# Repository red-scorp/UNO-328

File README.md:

# UNO/328 project

UNO/328 is a clone board of popular Arduino Uno board.
Main goal of the project is to improve EMC property of original board keeping it still simple and cheap to produce.

## Uno_v1.0

**Uno_v1.0** is version 1.0 of the board featuring CH340G USB to UART chip and ATMEGA328P as MCU.

Preview:

[Schematics in PDF format](doc/Uno_v1.0.pdf)

Features:

- Uno compatible board pinout
- Uno compatible MCU ATMEGA328P
- 2 layer board design
- alternative footprints for MCU: TQFP and HVQFN
- CH340G chip as USB to UART bridge
- modern microUSB connector
- possibly better EMC parameters (not yet tested)

CAM files are available.
BoM and PnP files for JLCPCB are available.

## Links

- CH340G Driver for Windows: [CH341SER_ZIP](http://www.wch.cn/download/CH341SER_ZIP.html)

## How to help

Your contributions as code, resources, or finances are welcome! Please contact me directly via email at andriy.golovnya@gmail.com or through my [GitHub profile](https://github.com/red-scorp).

If you'd like to make a financial contribution, you can donate via [PayPal](http://paypal.me/redscorp) or [Ko-Fi](http://ko-fi.com/redscorp). Your support is greatly appreciated.

Thanks in advance!

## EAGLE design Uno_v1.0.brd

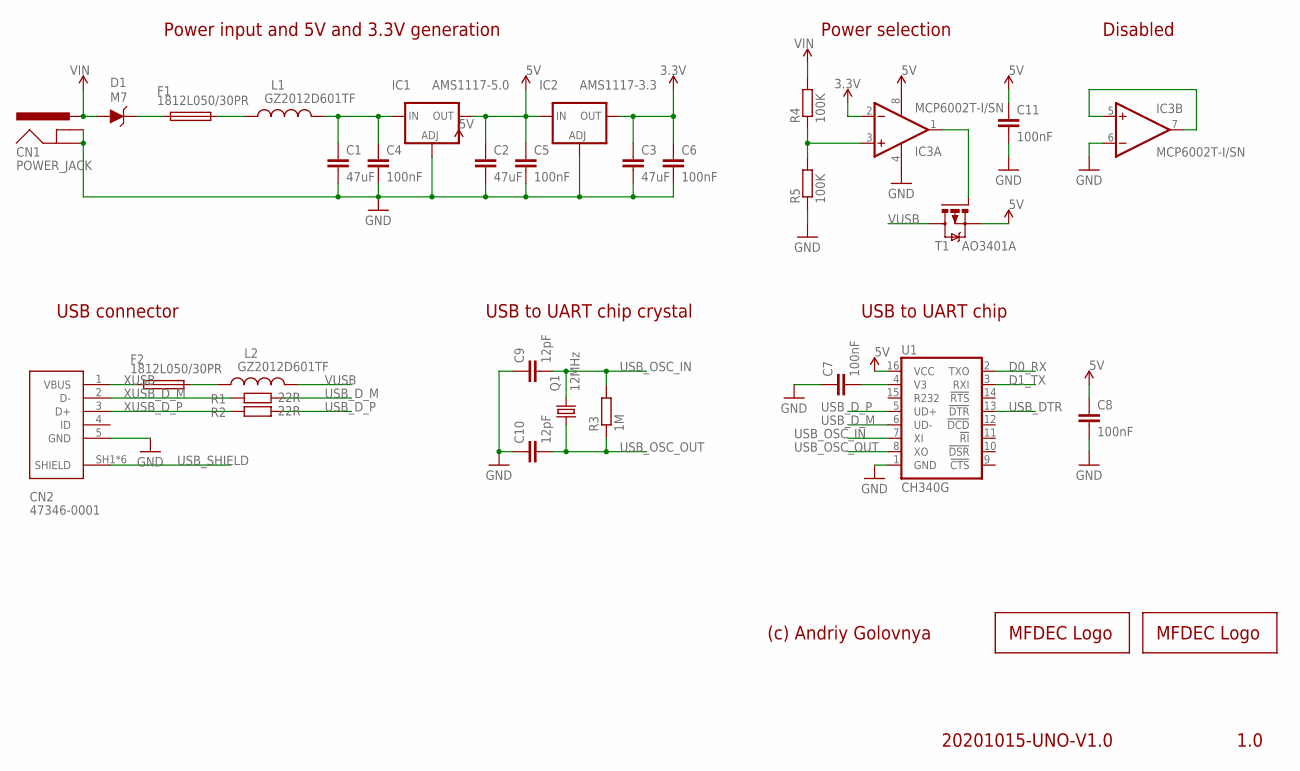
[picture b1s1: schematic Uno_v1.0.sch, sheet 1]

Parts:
C1, C2, C3: 47uF; C1206
C4, C5, C6, C7, C8, C11: 100nF; C0402
C9, C10: 12pF; C0402
CN1: POWER_JACK; POWER_JACK_PTH
CN2: 47346-0001; MOLEX_47346-0001
D1: M7; WE-TVSP_DO-214AC_UNIDIRECTIONAL
F1, F2: 1812L050/30PR; MF-SMDF050
IC1: AMS1117-5.0; SOT223
IC2: AMS1117-3.3; SOT223
IC3: MCP6002T-I/SN; SO08
L1, L2: GZ2012D601TF; WE-CBA_0805(W=4)
LOGO1: MFDECLOGO_SQ_10MM; MFDEC_SQ_10MM
LOGO2: MFDECLOGO_L_40MM; MFDEC_L_40MM
Q1: 12MHz; 3.2X2.5_KX-7
R1, R2: 22R; R0402
R3: 1M; R0402
R4, R5: 100K; R0402
T1: AO3401A; SOT23
U1: CH340G; SO016

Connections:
3.3V: C3.1, C6.1, IC2.4 (OUT), IC3.2 (-IN); also elsewhere on the board
5V: C2.1, C5.1, C8.1, C11.1, IC1.4 (OUT), IC2.3 (IN), IC3.8 (V+), T1.2 (S), U1.16 (VCC); also elsewhere on the board
D0_RX: U1.2 (TXO); also elsewhere on the board
D1_TX: U1.3 (RXI); also elsewhere on the board
unnamed: D1.1 (C), F1.1
unnamed: F1.2, L1.1
unnamed: F2.2, L2.1
unnamed: C7.2, U1.4 (V3)
unnamed: IC3.1 (OUT), T1.1 (G)
unnamed: IC3.3 (+IN), R4.1, R5.2
unnamed: C1.1, C4.1, IC1.3 (IN), L1.2
USB_DTR: U1.13 (!DTR); also elsewhere on the board
USB_D_M: R1.2, U1.6 (UD-)
USB_D_P: R2.2, U1.5 (UD+)
USB_OSC_IN: C9.2, Q1.3 (2), R3.2, U1.7 (XI)
USB_OSC_OUT: C10.2, Q1.1, R3.1, U1.8 (XO)
USB_SHIELD: CN2.SH1 (SHIELD), CN2.SH2 (SHIELD), CN2.SH3 (SHIELD), CN2.SH4 (SHIELD), CN2.SH5 (SHIELD), CN2.SH6 (SHIELD)
VIN: CN1.PWR, D1.2 (A), R4.2; also elsewhere on the board
VUSB: L2.2, T1.3 (D)
XUSB: CN2.1 (VBUS), F2.1
XUSB_D_M: CN2.2 (D-), R1.1
XUSB_D_P: CN2.3 (D+), R2.1

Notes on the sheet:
1.0
(c) Andriy Golovnya
20201015-UNO-V1.0
Power input and 5V and 3.3V generation
USB connector
USB to UART chip
USB to UART chip crystal
Power selection
Disabled

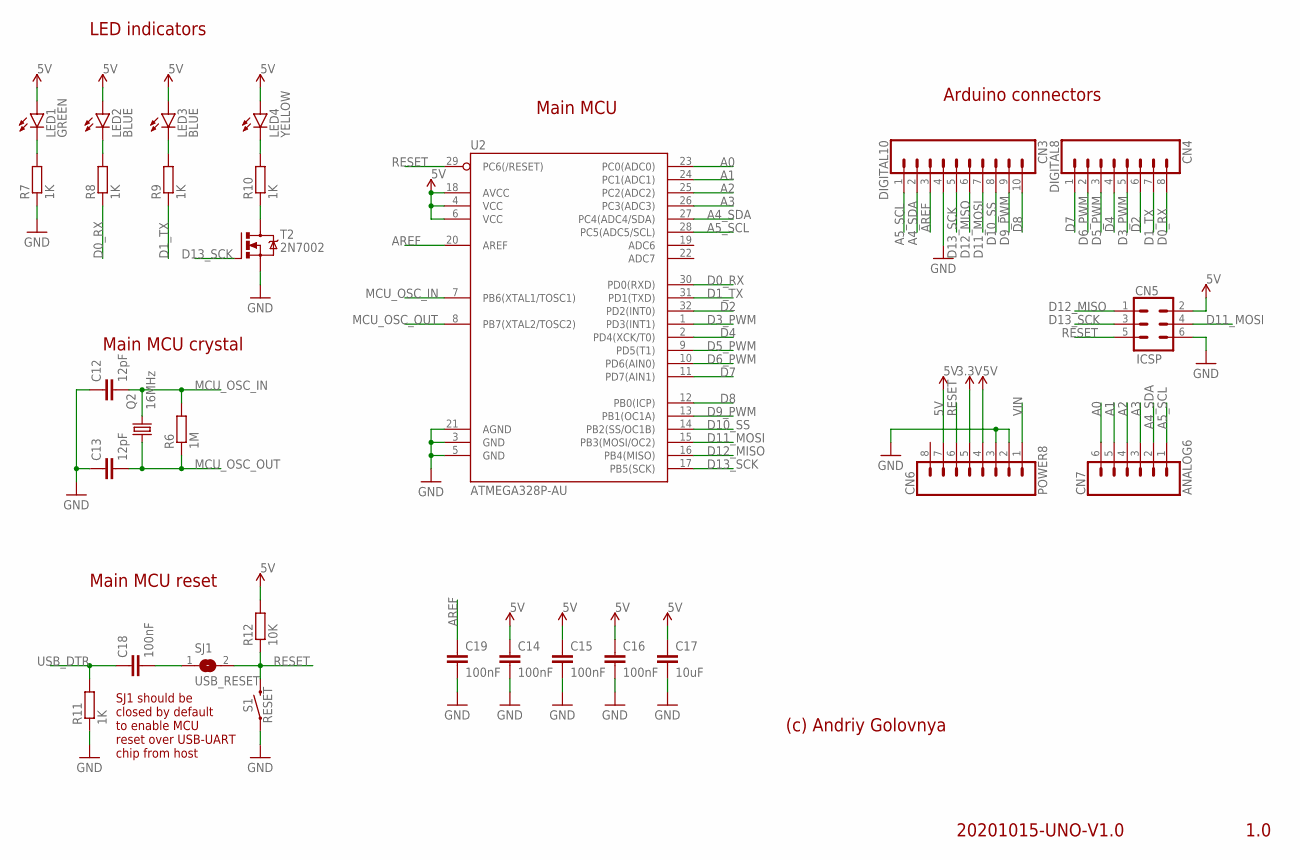
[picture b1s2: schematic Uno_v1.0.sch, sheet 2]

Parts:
C12, C13: 12pF; C0402
C14, C15, C16, C18, C19: 100nF; C0402
C17: 10uF; C0805
CN3: DIGITAL10; 1X10_NO_SILK
CN4: DIGITAL8; 1X08_NO_SILK
CN5: ICSP; 2X3-NS
CN6: POWER8; 1X08_NO_SILK
CN7: ANALOG6; 1X06_NO_SILK
LED1: GREEN; SML0603
LED2, LED3: BLUE; SML0603
LED4: YELLOW; SML0603
Q2: 16MHz; 3.2X2.5_KX-7
R6: 1M; R0402
R7, R8, R9, R10, R11: 1K; R0402
R12: 10K; R0402
S1: RESET; TACTILE_SWITCH_SMD_5.2MM
SJ1: USB_RESET; SJ
T2: 2N7002; SOT23
U2: ATMEGA328P-AU; TQFP32-08

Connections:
3.3V: CN6.5; also elsewhere on the board
5V: C14.1, C15.1, C16.1, C17.1, CN5.2, CN6.4, CN6.7, LED1.A, LED2.A, LED3.A, LED4.A, R12.2, U2.4 (VCC), U2.6 (VCC), U2.18 (AVCC); also elsewhere on the board
A0: CN7.6, U2.23 (PC0(ADC0)); also elsewhere on the board
A1: CN7.5, U2.24 (PC1(ADC1)); also elsewhere on the board
A2: CN7.4, U2.25 (PC2(ADC2)); also elsewhere on the board
A3: CN7.3, U2.26 (PC3(ADC3)); also elsewhere on the board
A4_SDA: CN3.2, CN7.2, U2.27 (PC4(ADC4/SDA)); also elsewhere on the board
A5_SCL: CN3.1, CN7.1, U2.28 (PC5(ADC5/SCL)); also elsewhere on the board
AREF: C19.1, CN3.3, U2.20 (AREF); also elsewhere on the board
D0_RX: CN4.8, R8.1, U2.30 (PD0(RXD)); also elsewhere on the board
D1_TX: CN4.7, R9.1, U2.31 (PD1(TXD)); also elsewhere on the board
D2: CN4.6, U2.32 (PD2(INT0)); also elsewhere on the board
D3_PWM: CN4.5, U2.1 (PD3(INT1)); also elsewhere on the board
D4: CN4.4, U2.2 (PD4(XCK/T0)); also elsewhere on the board
D5_PWM: CN4.3, U2.9 (PD5(T1)); also elsewhere on the board
D6_PWM: CN4.2, U2.10 (PD6(AIN0)); also elsewhere on the board
D7: CN4.1, U2.11 (PD7(AIN1)); also elsewhere on the board
D8: CN3.10, U2.12 (PB0(ICP)); also elsewhere on the board
D9_PWM: CN3.9, U2.13 (PB1(OC1A)); also elsewhere on the board
D10_SS: CN3.8, U2.14 (PB2(SS/OC1B)); also elsewhere on the board
D11_MOSI: CN3.7, CN5.4, U2.15 (PB3(MOSI/OC2)); also elsewhere on the board
D12_MISO: CN3.6, CN5.1, U2.16 (PB4(MISO)); also elsewhere on the board
D13_SCK: CN3.5, CN5.3, T2.1 (G), U2.17 (PB5(SCK)); also elsewhere on the board
MCU_OSC_IN: C12.2, Q2.3 (2), R6.2, U2.7 (PB6(XTAL1/TOSC1)); also elsewhere on the board
MCU_OSC_OUT: C13.2, Q2.1, R6.1, U2.8 (PB7(XTAL2/TOSC2)); also elsewhere on the board
unnamed: C18.2, SJ1.1
unnamed: LED1.C, R7.2
unnamed: LED3.C, R9.2
unnamed: LED2.C, R8.2
unnamed: LED4.C, R10.2
unnamed: R10.1, T2.3 (D)
RESET: CN5.5, CN6.6, R12.1, S1.3 (2), SJ1.2, U2.29 (PC6(/RESET)); also elsewhere on the board
USB_DTR: C18.1, R11.2; also elsewhere on the board
VIN: CN6.1; also elsewhere on the board

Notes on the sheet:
1.0
(c) Andriy Golovnya
20201015-UNO-V1.0
LED indicators
Main MCU
Main MCU reset
Arduino connectors
Main MCU crystal
SJ1 should be closed by default to enable MCU reset over USB-UART chip from host

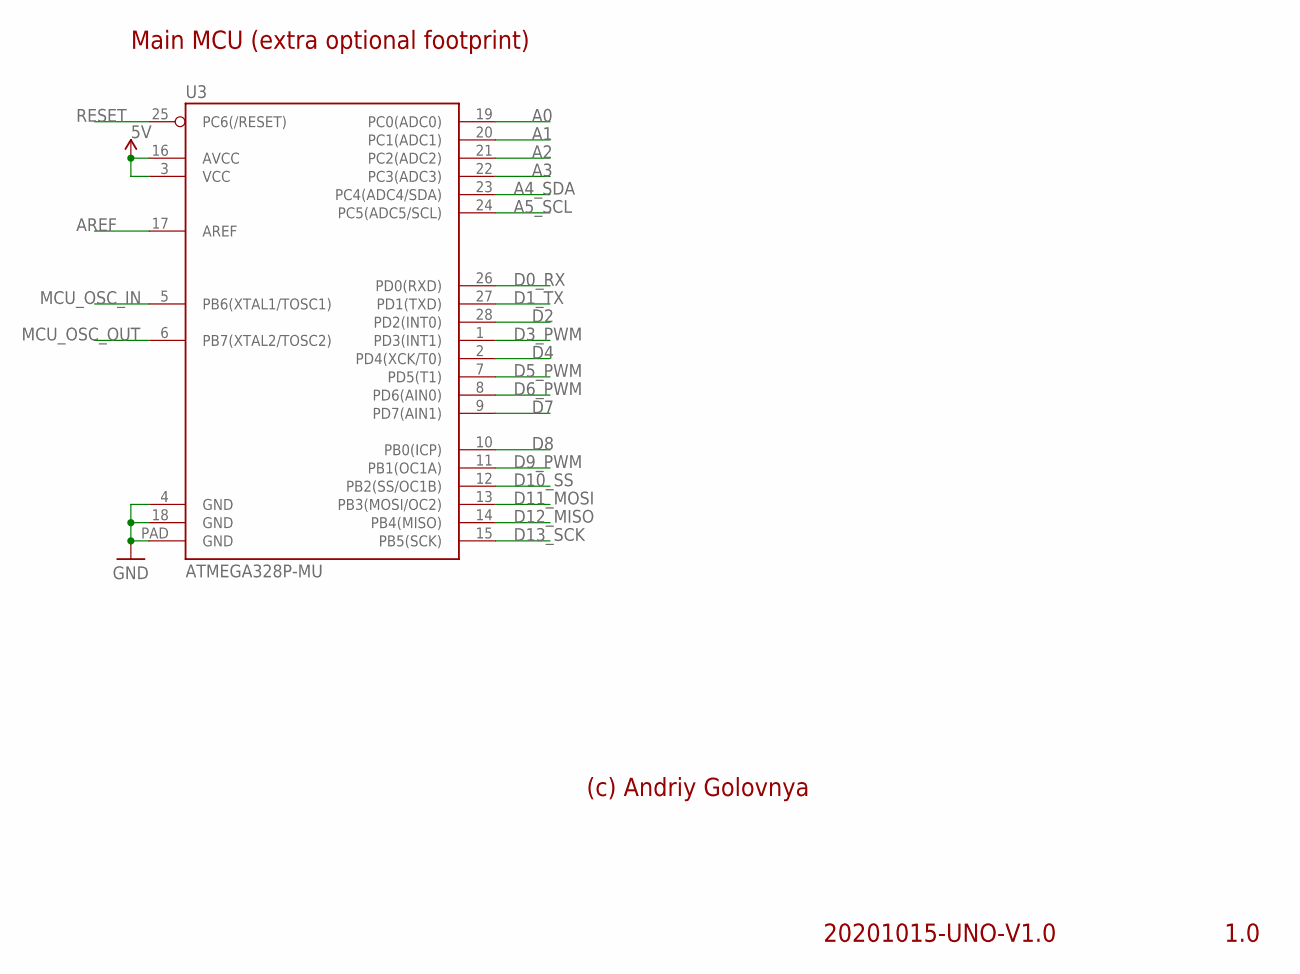
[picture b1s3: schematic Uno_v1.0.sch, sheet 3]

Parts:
U3: ATMEGA328P-MU; VQFN-28

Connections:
5V: U3.3 (VCC), U3.16 (AVCC); also elsewhere on the board
A0: U3.19 (PC0(ADC0)); also elsewhere on the board
A1: U3.20 (PC1(ADC1)); also elsewhere on the board
A2: U3.21 (PC2(ADC2)); also elsewhere on the board
A3: U3.22 (PC3(ADC3)); also elsewhere on the board
A4_SDA: U3.23 (PC4(ADC4/SDA)); also elsewhere on the board
A5_SCL: U3.24 (PC5(ADC5/SCL)); also elsewhere on the board
AREF: U3.17 (AREF); also elsewhere on the board
D0_RX: U3.26 (PD0(RXD)); also elsewhere on the board
D1_TX: U3.27 (PD1(TXD)); also elsewhere on the board
D2: U3.28 (PD2(INT0)); also elsewhere on the board
D3_PWM: U3.1 (PD3(INT1)); also elsewhere on the board
D4: U3.2 (PD4(XCK/T0)); also elsewhere on the board
D5_PWM: U3.7 (PD5(T1)); also elsewhere on the board
D6_PWM: U3.8 (PD6(AIN0)); also elsewhere on the board
D7: U3.9 (PD7(AIN1)); also elsewhere on the board
D8: U3.10 (PB0(ICP)); also elsewhere on the board
D9_PWM: U3.11 (PB1(OC1A)); also elsewhere on the board
D10_SS: U3.12 (PB2(SS/OC1B)); also elsewhere on the board
D11_MOSI: U3.13 (PB3(MOSI/OC2)); also elsewhere on the board
D12_MISO: U3.14 (PB4(MISO)); also elsewhere on the board
D13_SCK: U3.15 (PB5(SCK)); also elsewhere on the board
MCU_OSC_IN: U3.5 (PB6(XTAL1/TOSC1)); also elsewhere on the board
MCU_OSC_OUT: U3.6 (PB7(XTAL2/TOSC2)); also elsewhere on the board
RESET: U3.25 (PC6(/RESET)); also elsewhere on the board

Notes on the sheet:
1.0
(c) Andriy Golovnya
20201015-UNO-V1.0
Main MCU (extra optional footprint)

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
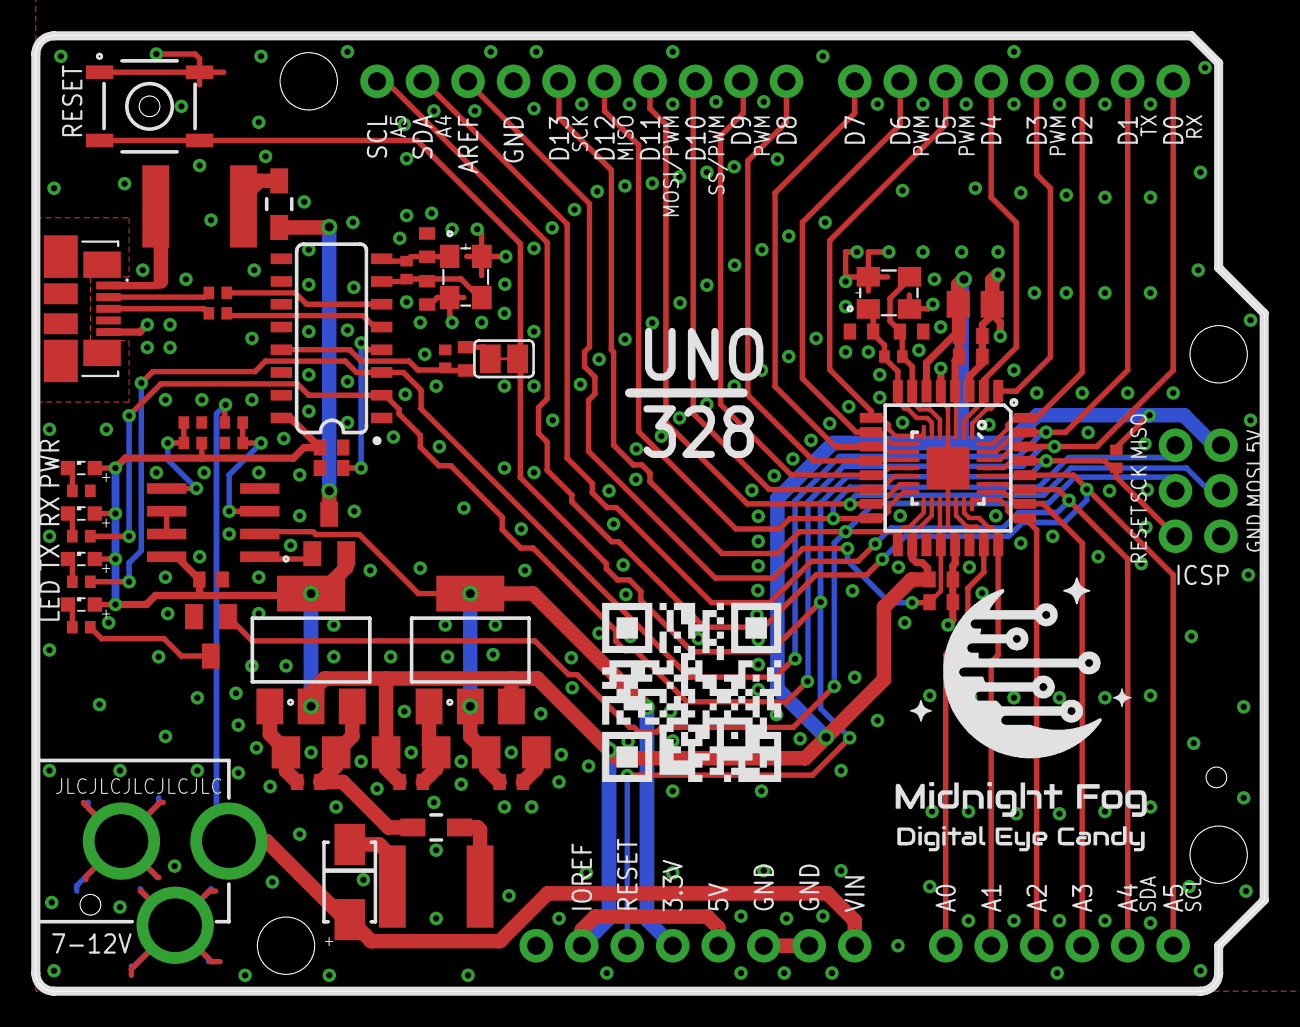
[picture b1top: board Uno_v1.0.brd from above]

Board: 2 copper layers, 68.6 x 53.3 mm, 67 parts (1 on the bottom side), 53 nets.

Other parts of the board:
HOLE1, HOLE2, HOLE3: TOOLINGHOLE; TOOLING-HOLE
LOGO3: RSNURL_QR_10MM
R13, R14: 100K; R0402

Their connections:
5V: R13.2; also elsewhere on the board

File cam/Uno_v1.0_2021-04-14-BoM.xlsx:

Qty | Designator | Footprint | Comment | LCSC Part # | Description
3 | C1, C2, C3 | 1206 | 47uF | C96123 | CAPACITOR, European symbol
1 | C17 | 0805 | 10uF | C15850 | CAPACITOR, European symbol
11 | C4, C5, C6, C7, C8, C11, C14, C15, C16, C18, C19 | 0402 | 100nF | C1525 | CAPACITOR, European symbol
4 | C9, C10, C12, C13 | 0402 | 12pF | C1547 | CAPACITOR, European symbol
1 | D1 | SMA,DO-214AC | M7 | C95872 | WE-TVSP Power TVS Diode
2 | F1, F2 | 1812 | 1812L050/30PR | C151168 | MF-SMDF Series - PRC Resettable Fuses
1 | IC1 | SOT-223 | AMS1117-5.0 | C6187 | Low drop fixed and adjustable positive voltage regulators 1 A
1 | IC2 | SOT-223 | AMS1117-3.3 | C6186 | Low drop fixed and adjustable positive voltage regulators 1 A
1 | IC3 | SOIC-8_3.9x4.9x1.27P | LM358DR2G | C7950 | OpAmp
2 | L1, L2 | 0805 | GZ2012D601TF | C1017 | WE-CBA SMD EMI Suppression Ferrite Bead
1 | LED1 | LED_0603 | GREEN | C72043 | LED
2 | LED2, LED3 | LED_0603 | BLUE | C72041 | LED
1 | LED4 | LED_0603 | YELLOW | C72038 | LED
1 | Q1 | SMD-3225_4P | 12MHz | C9002 | Quartz Crystals (MHz) SMD:
1 | Q2 | SMD-3225_4P | 16MHz | C13738 | Quartz Crystals (MHz) SMD:
2 | R1, R2 | 0402 | 22R | C25092 | RESISTOR, European symbol
1 | R12 | 0402 | 10K | C25744 | RESISTOR, European symbol
2 | R3, R6 | 0402 | 1M | C26083 | RESISTOR, European symbol
4 | R4, R5, R13, R14 | 0402 | 100K | C25741 | RESISTOR, European symbol
5 | R7, R8, R9, R10, R11 | 0402 | 1K | C11702 | RESISTOR, European symbol
1 | T1 | SOT-23-3L | AO3401A | C15127 | P-Channel MOSFET - Generic
1 | T2 | SOT-23-3 | 2N7002 | C8545 | N-Channel MOSFET - Generic
1 | U1 | SOIC-16_3.9x9.9x1.27P | CH340G | C14267 | A simple USB 2.0 to Serial IC.
1 | U2 | TQFP-32_7.0x7.0x0.8P | ATMEGA328P-AU | C14877 | Popular 328P in QFP

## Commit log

2020-10-17 First commit in Uno repo
2020-10-17 Add some traces
2020-10-18 Add some wires. Add top/bottom fills. Add top/bottom silks. Add pin descriptions.
2020-10-18 Minor adjustments
2020-10-19 Fix connection of V3 pin of CH340G
2020-10-23 Change capacitor sizes. Move stuff around.
2020-10-24 Move stuff around. Change how SJ1 is closed by default. Add ground connections to Q2 and reset button.
2020-10-27 Add second footprint for atmega328. Move components a little.
2020-10-27 Rotated CH340G 180 degrees. Moved stuff around a little.
2020-10-29 Move some stuff around
2020-10-30 Move stuff around
2020-10-30 Move stuff around.
2020-10-30 Add RSN URL to the board. Moved DTR-reset group closed to CH340G.
2020-10-30 Add project description
2020-10-30 some eagle internal stuff
2020-11-01 Added CAM, BOM and PaP files for JLCPCB. Move some stuff around.
2020-11-02 Fix MOSI label. Moved UNO logo a little.
2020-11-04 Added extra pin descriptions. Moved UNO logo up a bit. Generated new CAM.
2020-11-07 Approved something in ERC.
2020-11-13 Add extra fancy connections around power jack ground
2020-11-22 Fix document number
2020-12-05 Changed some traces. Moved few components a little.
2020-12-05 Generated new CAM and PaP. BOM remains the same.
2020-12-06 Moved few vias.
2020-12-06 Generated new CAM.
2020-12-06 Added white frame around the board.
2021-01-16 tried to fix BOM and PaP for JLCPCB
2021-04-12 Moved main MCU a little bit to the right. Generated new CAM. Generated new preview.
2021-04-12 Restored old BOM. Generated new PnP.
2021-04-12 Moved some wires. Generated new CAM. Generated new preview.
2021-04-13 Use LM358D OpAmp instead. Generated new CAM. Generated new PNG preview. Generated new PDF schematic.
2021-04-14 Properly disabled second channel of op amp. Generated new CAM files. Generated new PNG preview. Generated new PDF schematics. Generated new BoM and PnP files.
2021-04-14 Fixed unconnected symbol on schematics. Generated new PDF schematics. Fixed BoM and PnP files for JLCPB assembly.
2021-05-02 Redone chip wiring for better reverse currents.
2021-05-02 Generated PDF schematics. Generated PNG preview.
2021-05-02 Generated CAM files.
2021-05-02 Generated BoM and PnP files.
2021-05-03 Moved some traces around.
2021-05-03 Generated PNG preview.
2021-05-04 Created README.
2021-05-05 Added FUNDING.yml
2021-05-05 Generate CAM files. Updated BoM file.
2021-05-05 Updated descriptions
2021-05-06 Added JLCPCB tooling holes and order number placement.
2021-05-14 Changed few components to do manufacturing possible.
2021-08-21 Made secondary texts bigger. Generated CAM files. Generated PNG preview.
2021-12-05 cleanup.
2022-01-24 Added Ko-Fi link
2023-08-28 Updated 'How to help' section.

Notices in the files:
parts and their libraries:
Wurth_Automotive_WE-CBA: Copyright: Würth Elektronik
SparkFun-IC-Comms: Licensing: Creative Commons ShareAlike 4.0 International - https://creativecommons.org/licenses/by-sa/4.0
crystal-geyer_V1_0: Copyright: Geyer-Electronic
